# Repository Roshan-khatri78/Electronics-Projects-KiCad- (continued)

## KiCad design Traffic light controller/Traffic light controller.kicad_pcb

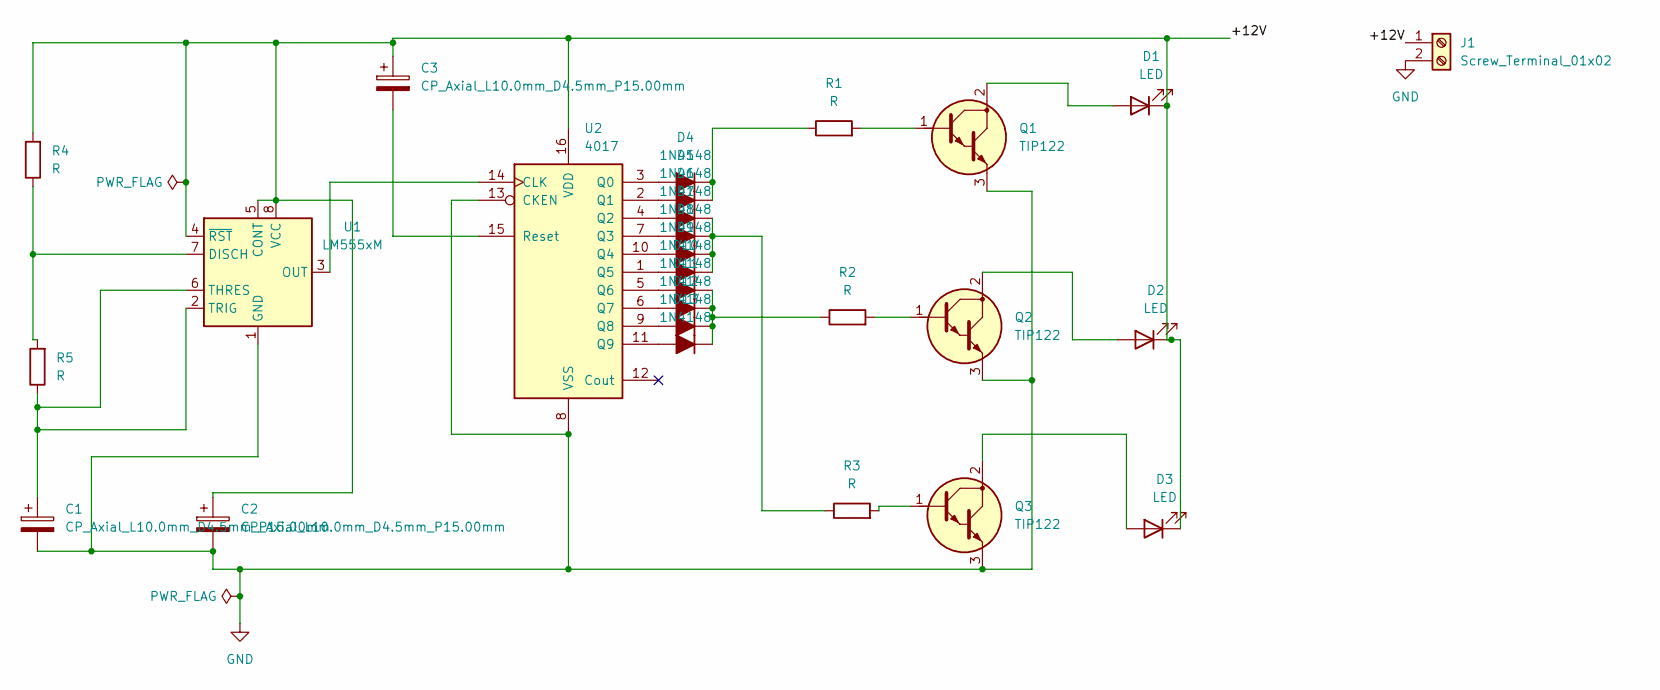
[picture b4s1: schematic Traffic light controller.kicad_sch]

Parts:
C1, C2, C3: CP_Axial_L10.0mm_D4.5mm_P15.00mm; CP_Axial_L10.0mm_D4.5mm_P15.00mm_Horizontal
D1, D2, D3: LED; LED_D5.0mm
D4, D5, D6, D7, D8, D9, D10, D11, D12, D13: 1N4148; D_5W_P12.70mm_Horizontal
J1: Screw_Terminal_01x02; TerminalBlock_MaiXu_MX126-5.0-02P_1x02_P5.00mm
Q1, Q2, Q3: TIP122; TO-220-3_Vertical_BCE
R1, R2, R3, R4, R5: R; R_Axial_DIN0204_L3.6mm_D1.6mm_P1.90mm_Vertical
U1: LM555xM; SOIC-8_3.9x4.9mm_P1.27mm
U2: 4017; DIP-16_W10.16mm

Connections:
/+12V: C2.1, C3.1, D1.1 (K), D2.1 (K), D3.1 (K), J1.1, R4.2, U1.4 (~RST), U1.5 (CONT), U1.8 (VCC), U2.16 (VDD)
GND: C1.2, C2.2, J1.2, Q1.3 (E), Q2.3 (E), Q3.3 (E), U1.1 (GND), U2.8 (VSS), U2.13 (CKEN)
unnamed: D1.2 (A), Q1.2 (C)
unnamed: D2.2 (A), Q2.2 (C)
unnamed: D3.2 (A), Q3.2 (C)
unnamed: D4.2 (A), U2.3 (Q0)
unnamed: D4.1 (K), D5.1 (K), R1.1
unnamed: D5.2 (A), U2.2 (Q1)
unnamed: D6.2 (A), U2.4 (Q2)
unnamed: D6.1 (K), D7.1 (K), D8.1 (K), D9.1 (K), R3.1
unnamed: D7.2 (A), U2.7 (Q3)
unnamed: D8.2 (A), U2.10 (Q4)
unnamed: D9.2 (A), U2.1 (Q5)
unnamed: D10.2 (A), U2.5 (Q6)
unnamed: D10.1 (K), D11.1 (K), D12.1 (K), D13.1 (K), R2.1
unnamed: D11.2 (A), U2.6 (Q7)
unnamed: D12.2 (A), U2.9 (Q8)
unnamed: D13.2 (A), U2.11 (Q9)
unnamed: Q1.1 (B), R1.2
unnamed: Q2.1 (B), R2.2
unnamed: Q3.1 (B), R3.2
unnamed: R4.1, R5.2, U1.7 (DISCH)
unnamed: U1.3 (OUT), U2.14 (CLK)
unnamed: C1.1, R5.1, U1.2 (TRIG), U1.6 (THRES)
unnamed: C3.2, U2.15 (Reset)

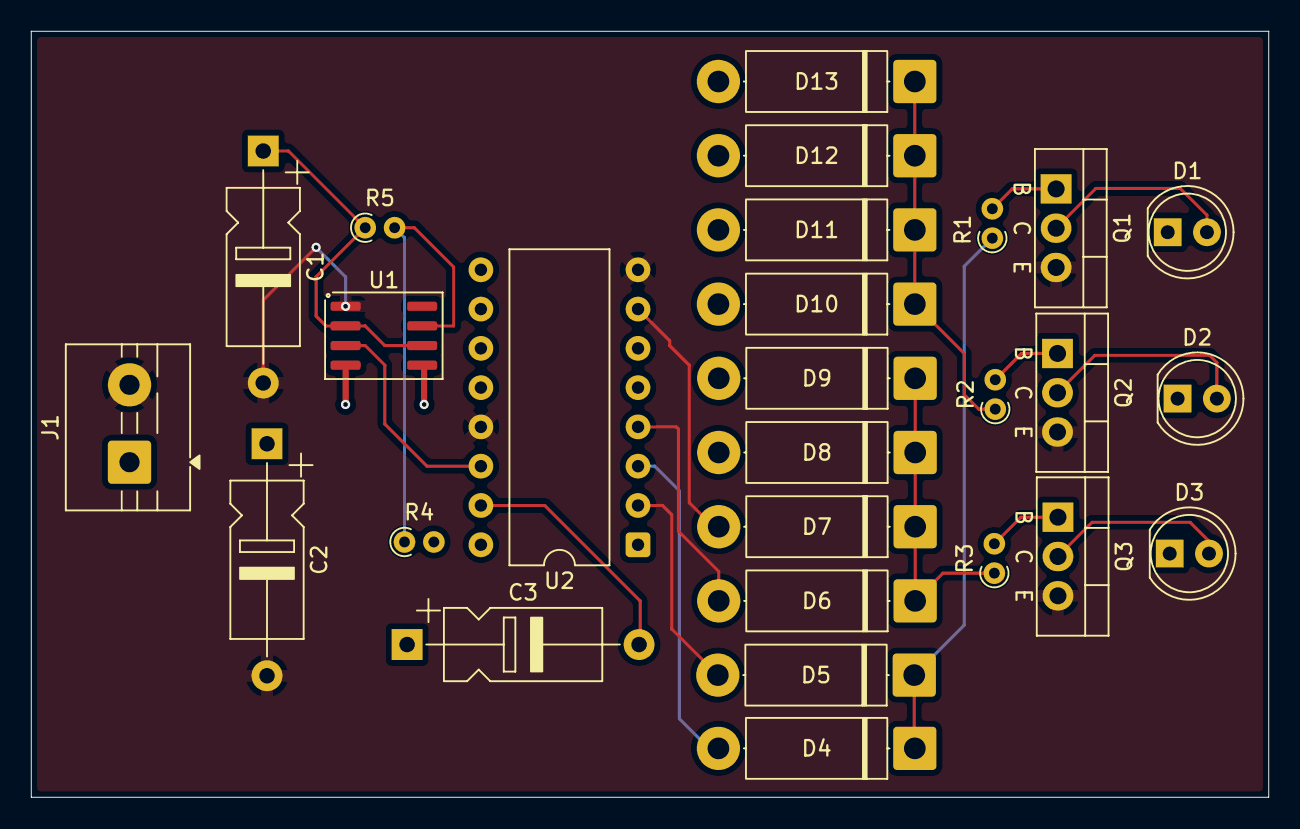
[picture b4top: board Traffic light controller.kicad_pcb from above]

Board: 4 copper layers, 80.0 x 49.5 mm, 27 parts (0 on the bottom side), 25 nets.

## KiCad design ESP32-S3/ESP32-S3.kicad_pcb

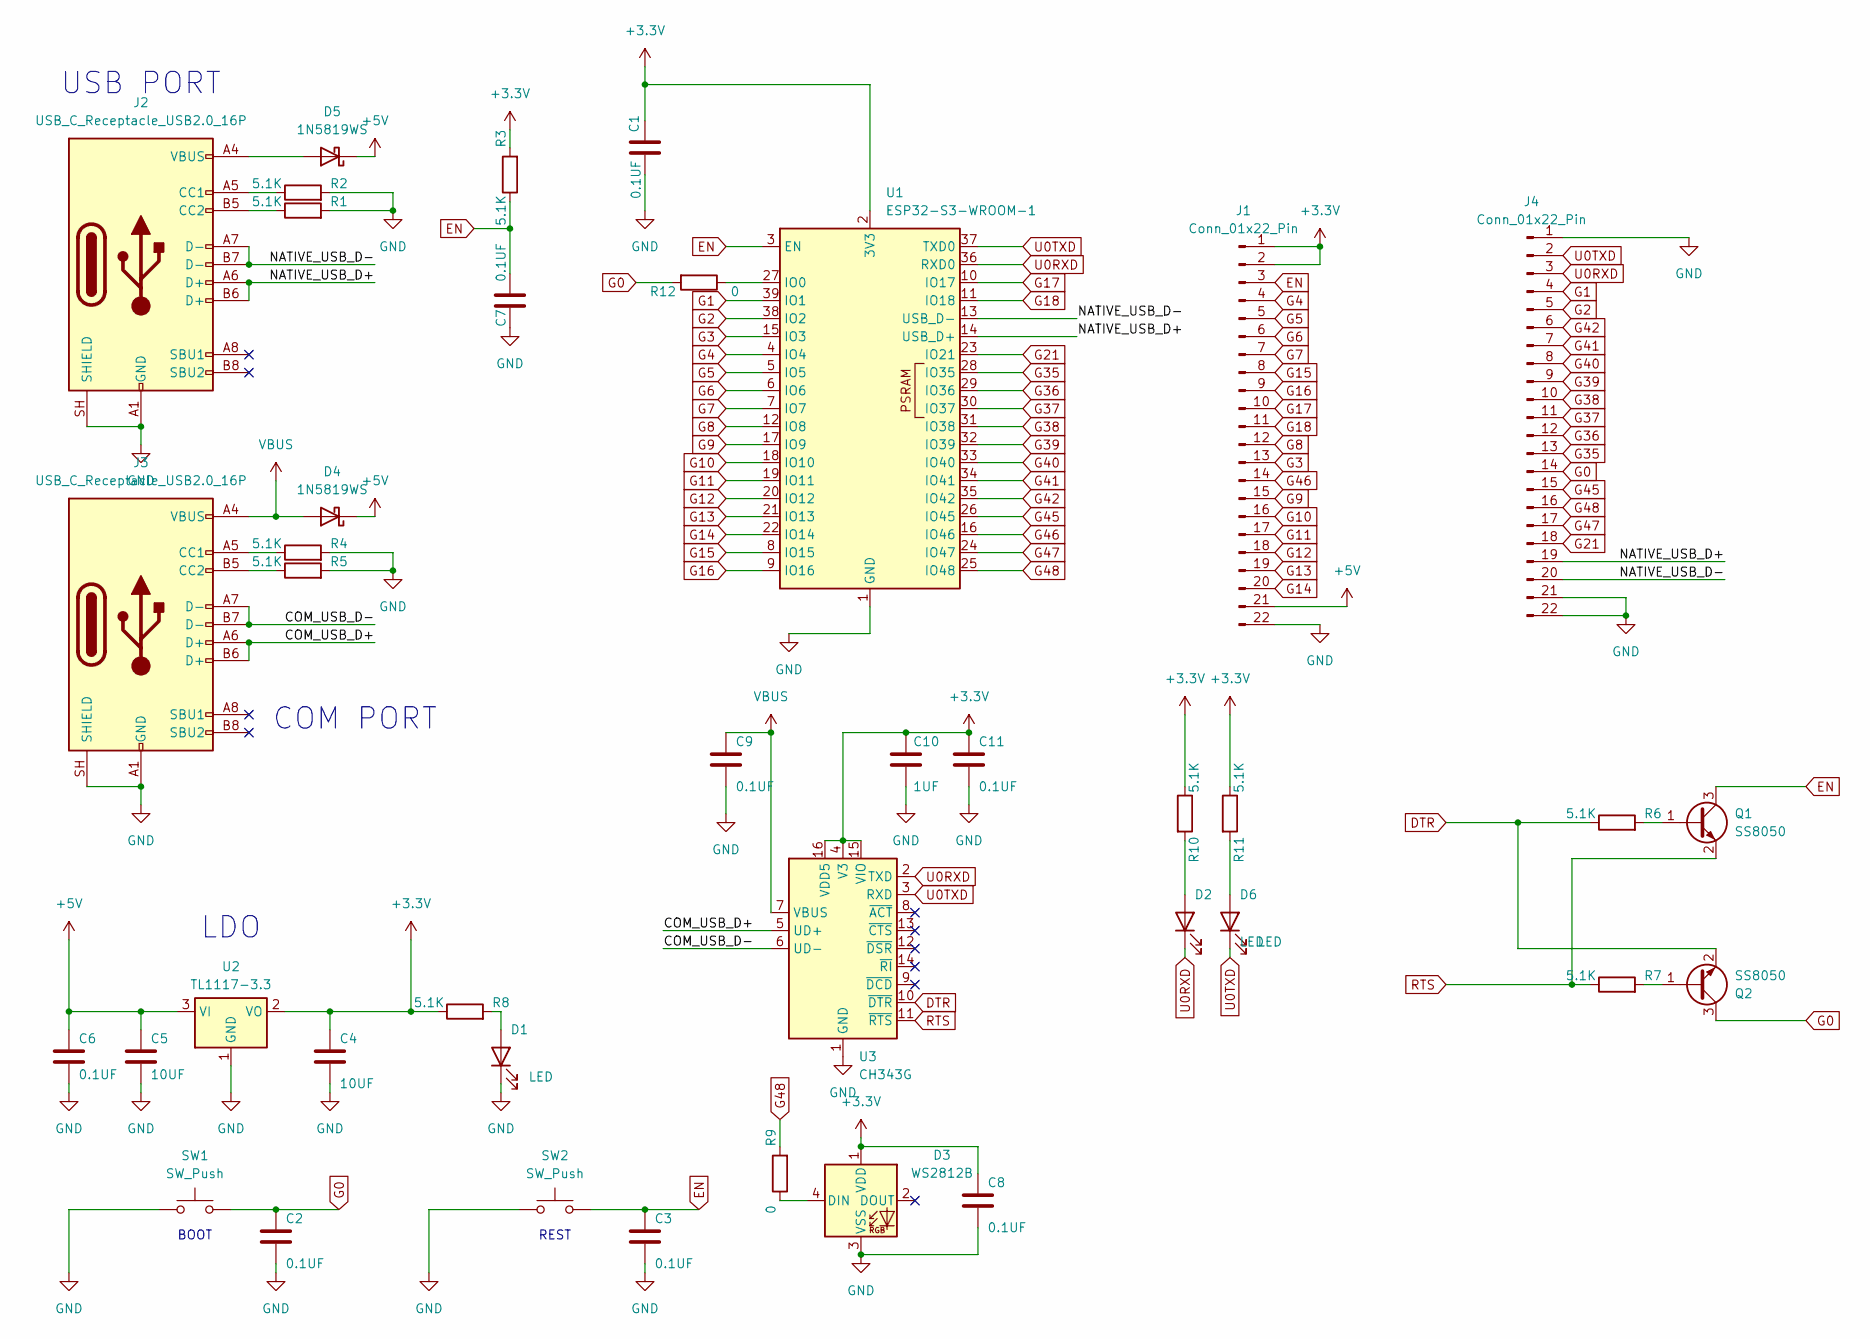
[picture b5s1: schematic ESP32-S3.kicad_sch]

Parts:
C1, C2, C3, C6, C7, C8, C9, C11: 0.1UF; C_0603_1608Metric
C4, C5: 10UF; C_0805_2012Metric
C10: 1UF; C_0603_1608Metric
D1, D2, D6: LED; LED_0603_1608Metric_Pad1.05x0.95mm_HandSolder
D3: WS2812B; LED_WS2812B_PLCC4_5.0x5.0mm_P3.2mm
D4, D5: 1N5819WS; D_SOD-323
J1, J4: Conn_01x22_Pin; PinHeader_1x22_P2.54mm_Vertical
J2, J3: USB_C_Receptacle_USB2.0_16P; USB_C_Receptacle_GCT_USB4105-xx-A_16P_TopMnt_Horizontal
Q1, Q2: SS8050; SOT-23
R1, R2, R3, R4, R5, R6, R7, R8, R10, R11: 5.1K; R_0603_1608Metric
R9, R12: 0; R_0603_1608Metric
SW1, SW2: SW_Push; SW_SPST_PTS810
U1: ESP32-S3-WROOM-1
U2: TL1117-3.3; SOT-223-3_TabPin2
U3: CH343G; SOIC-16_3.9x9.9mm_P1.27mm

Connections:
+3.3V: C1.1, C4.1, C8.1, C10.2, C11.2, D3.1 (VDD), J1.1, J1.2, R3.2, R8.1, R10.1, R11.1, U1.2 (3V3), U2.2 (VO), U3.4 (V3), U3.15 (VIO), U3.16 (VDD5)
+5V: C5.1, C6.1, D4.1 (K), D5.1 (K), J1.21, U2.3 (VI)
/COM_USB_D+: J3.A6 (D+), J3.B6 (D+), U3.5 (UD+)
/COM_USB_D-: J3.A7 (D-), J3.B7 (D-), U3.6 (UD-)
/NATIVE_USB_D+: J2.A6 (D+), J2.B6 (D+), J4.19, U1.14 (USB_D+)
/NATIVE_USB_D-: J2.A7 (D-), J2.B7 (D-), J4.20, U1.13 (USB_D-)
DTR: Q2.2 (E), R6.1, U3.10 (~DTR)
EN: C3.1, C7.1, J1.3, Q1.3 (C), R3.1, SW2.2, U1.3 (EN); also elsewhere on the board
G0: C2.1, J4.14, Q2.3 (C), R12.2, SW1.2; also elsewhere on the board
G1: J4.4, U1.39 (IO1)
G2: J4.5, U1.38 (IO2)
G3: J1.13, U1.15 (IO3)
G4: J1.4, U1.4 (IO4)
G5: J1.5, U1.5 (IO5)
G6: J1.6, U1.6 (IO6)
G7: J1.7, U1.7 (IO7)
G8: J1.12, U1.12 (IO8)
G9: J1.15, U1.17 (IO9)
G10: J1.16, U1.18 (IO10)
G11: J1.17, U1.19 (IO11)
G12: J1.18, U1.20 (IO12)
G13: J1.19, U1.21 (IO13)
G14: J1.20, U1.22 (IO14)
G15: J1.8, U1.8 (IO15)
G16: J1.9, U1.9 (IO16)
G17: J1.10, U1.10 (IO17)
G18: J1.11, U1.11 (IO18)
G21: J4.18, U1.23 (IO21)
G35: J4.13, U1.28 (IO35)
G36: J4.12, U1.29 (IO36)
G37: J4.11, U1.30 (IO37)
G38: J4.10, U1.31 (IO38)
G39: J4.9, U1.32 (IO39)
G40: J4.8, U1.33 (IO40)
G41: J4.7, U1.34 (IO41)
G42: J4.6, U1.35 (IO42)
G45: J4.15, U1.26 (IO45)
G46: J1.14, U1.16 (IO46)
G47: J4.17, U1.24 (IO47)
G48: J4.16, R9.2, U1.25 (IO48)
GND: C1.2, C2.2, C3.2, C4.2, C5.2, C6.2, C7.2, C8.2, C9.1, C10.1, C11.1, D1.1 (K), D3.3 (VSS), J1.22, J2.A1 (GND), J2.A12 (GND), J2.B1 (GND), J2.B12 (GND), J2.SH (SHIELD), J3.A1 (GND), J3.A12 (GND), J3.B1 (GND), J3.B12 (GND), J3.SH (SHIELD), J4.1, J4.21, J4.22, R1.2, R2.2, R4.2, R5.2, SW1.1, SW2.1, U1.1 (GND), U1.40 (GND), U1.41 (GND), U2.1 (GND), U3.1 (GND); also elsewhere on the board
unnamed: D1.2 (A), R8.2
unnamed: D2.2 (A), R10.2
unnamed: D3.4 (DIN), R9.1
unnamed: D5.2 (A), J2.A4 (VBUS), J2.A9 (VBUS), J2.B4 (VBUS), J2.B9 (VBUS)
unnamed: D6.2 (A), R11.2
unnamed: J2.A5 (CC1), R2.1
unnamed: J2.B5 (CC2), R1.1
unnamed: J3.A5 (CC1), R4.1
unnamed: J3.B5 (CC2), R5.1
unnamed: Q1.1 (B), R6.2
unnamed: Q2.1 (B), R7.2
unnamed: R12.1, U1.27 (IO0)
RTS: Q1.2 (E), R7.1, U3.11 (~RTS)
U0RXD: D2.1 (K), J4.3, U1.36 (RXD0), U3.2 (TXD)
U0TXD: D6.1 (K), J4.2, U1.37 (TXD0), U3.3 (RXD)
VBUS: C9.2, D4.2 (A), J3.A4 (VBUS), J3.A9 (VBUS), J3.B4 (VBUS), J3.B9 (VBUS), U3.7 (VBUS)

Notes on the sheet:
COM PORT
REST
LDO
USB PORT
BOOT

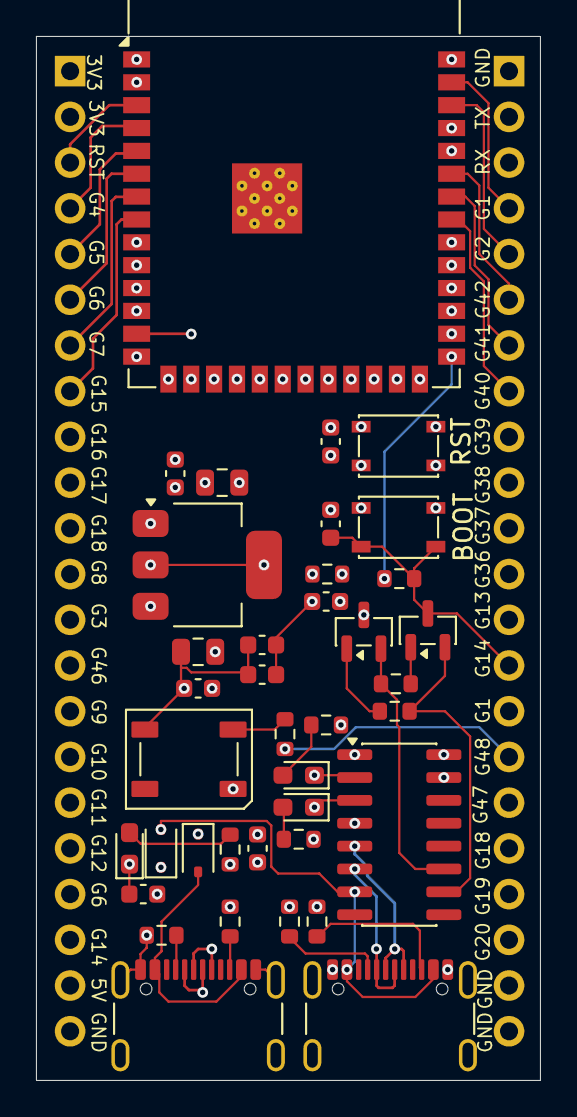
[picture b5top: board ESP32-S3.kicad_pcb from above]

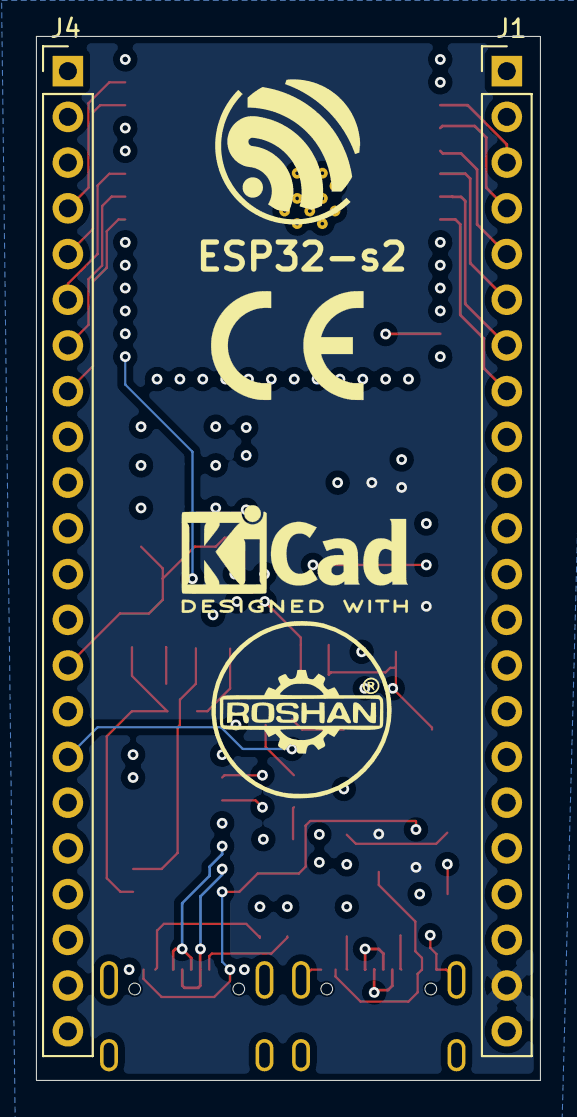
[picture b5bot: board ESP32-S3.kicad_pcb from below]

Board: 4 copper layers, 28.0 x 58.0 mm, 40 parts (2 on the bottom side), 57 nets.

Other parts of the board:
BOOT: SW_Push; SW_SPST_PTS810
RST: SW_Push; SW_SPST_PTS810

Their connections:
EN: RST.2; also elsewhere on the board
G0: BOOT.2; also elsewhere on the board
GND: BOOT.1, RST.1; also elsewhere on the board

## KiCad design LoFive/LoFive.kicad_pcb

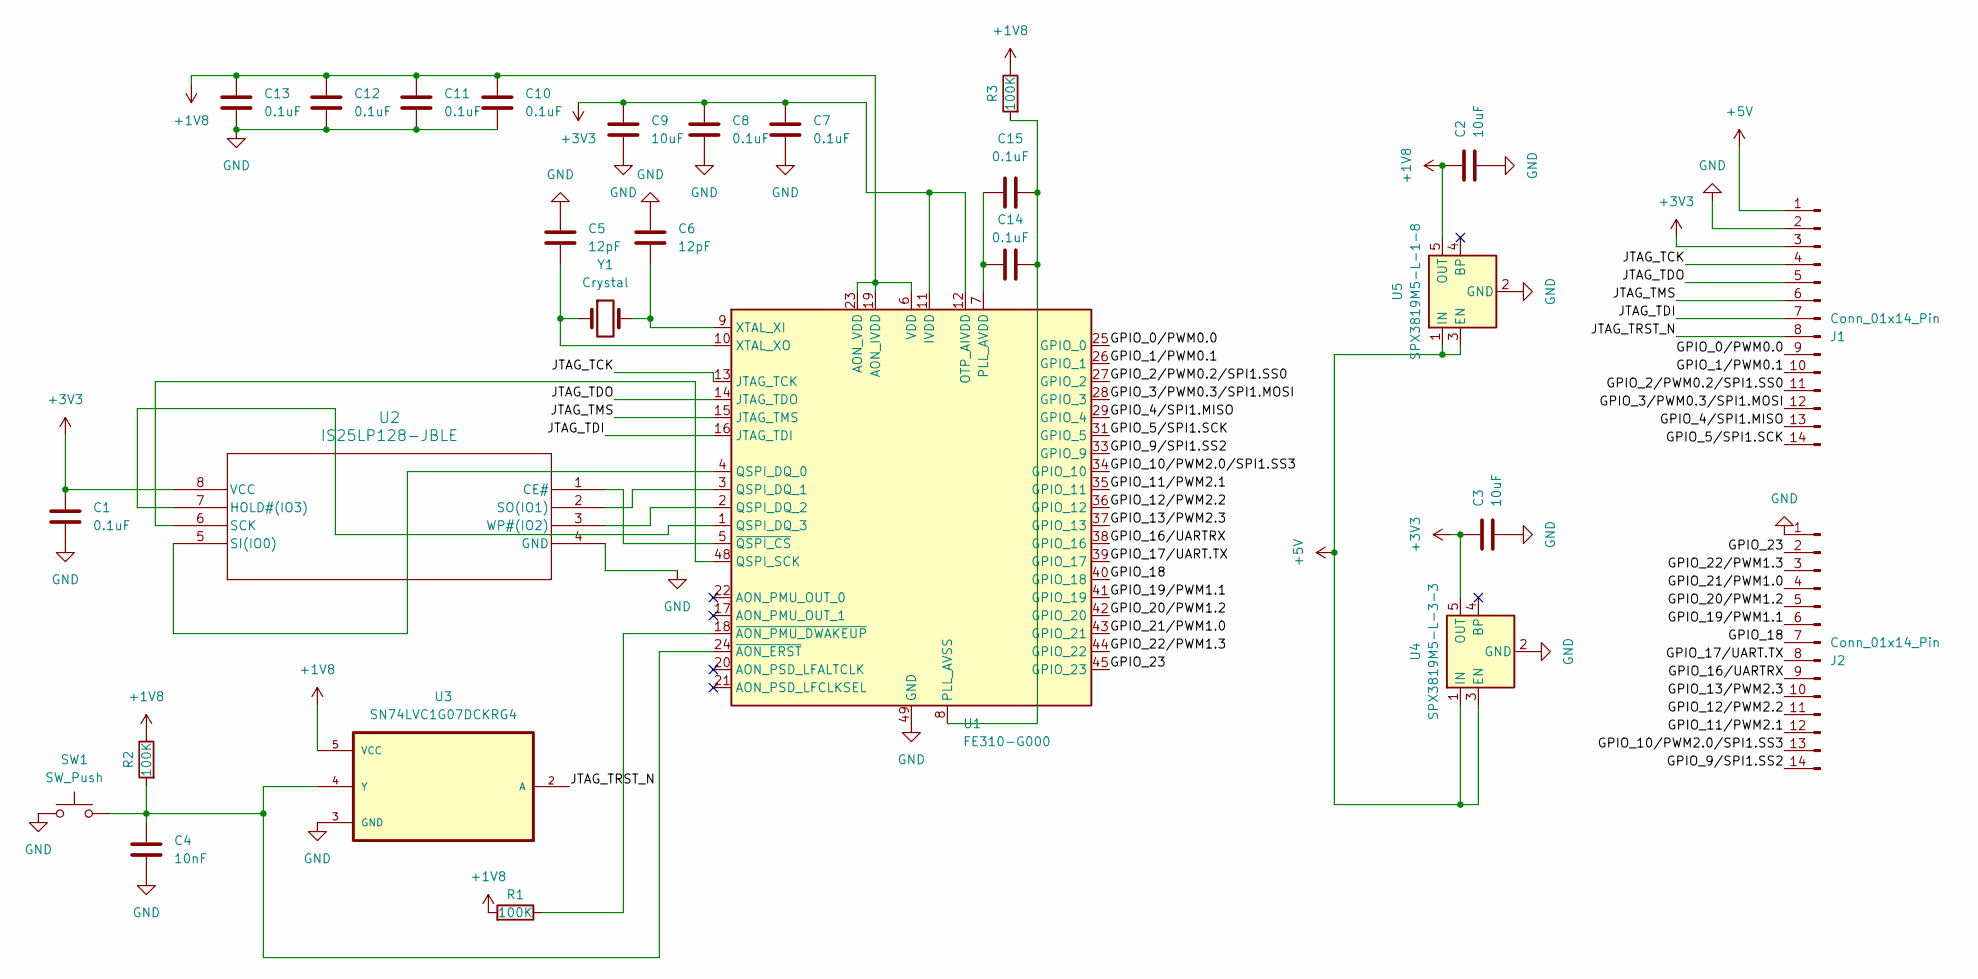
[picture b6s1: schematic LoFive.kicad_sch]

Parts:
C1, C7, C8, C10, C11, C12, C13, C14, C15: 0.1uF; C_0402_1005Metric_Pad0.74x0.62mm_HandSolder
C2, C3, C9: 10uF; C_0402_1005Metric_Pad0.74x0.62mm_HandSolder
C4: 10nF; C_0402_1005Metric_Pad0.74x0.62mm_HandSolder
C5, C6: 12pF; C_0402_1005Metric_Pad0.74x0.62mm_HandSolder
J1, J2: Conn_01x14_Pin; PinHeader_1x14_P2.54mm_Vertical
R1, R2, R3: 100K; R_0402_1005Metric_Pad0.72x0.64mm_HandSolder
SW1: SW_Push; SW_PUSH_6mm_H5mm
U1: FE310-G000; QFN-48-1EP_6x6mm_P0.4mm_EP4.2x4.2mm_ThermalVias
U2: IS25LP128-JBLE; SOIC8_208MIL_JB_ISI-M
U3: SN74LVC1G07DCKRG4; SOT65P210X110-5N
U4: SPX3819M5-L-3-3; SOT-23-5
U5: SPX3819M5-L-1-8; SOT-23-5
Y1: Crystal; Crystal_SMD_HC49-SD

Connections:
+1V8: C2.1, C10.1, C11.1, C12.1, C13.1, R1.1, R2.2, R3.2, U1.6 (VDD), U1.19 (AON_IVDD), U1.23 (AON_VDD), U1.30 (VDD), U1.46 (VDD), U3.5 (VCC), U5.5 (OUT)
+3V3: C1.1, C3.1, C7.1, C8.1, C9.1, J1.3, U1.11 (IVDD), U1.12 (OTP_AIVDD), U1.32 (IVDD), U1.47 (IVDD), U2.8 (VCC), U4.5 (OUT)
+5V: J1.1, U4.1 (IN), U4.3 (EN), U5.1 (IN), U5.3 (EN)
/GPIO_0/PWM0.0: J1.9, U1.25 (GPIO_0)
/GPIO_1/PWM0.1: J1.10, U1.26 (GPIO_1)
/GPIO_2/PWM0.2/SPI1.SS0: J1.11, U1.27 (GPIO_2)
/GPIO_3/PWM0.3/SPI1.MOSI: J1.12, U1.28 (GPIO_3)
/GPIO_4/SPI1.MISO: J1.13, U1.29 (GPIO_4)
/GPIO_5/SPI1.SCK: J1.14, U1.31 (GPIO_5)
/GPIO_9/SPI1.SS2: J2.14, U1.33 (GPIO_9)
/GPIO_10/PWM2.0/SPI1.SS3: J2.13, U1.34 (GPIO_10)
/GPIO_11/PWM2.1: J2.12, U1.35 (GPIO_11)
/GPIO_12/PWM2.2: J2.11, U1.36 (GPIO_12)
/GPIO_13/PWM2.3: J2.10, U1.37 (GPIO_13)
/GPIO_16/UARTRX: J2.9, U1.38 (GPIO_16)
/GPIO_17/UART.TX: J2.8, U1.39 (GPIO_17)
/GPIO_18: J2.7, U1.40 (GPIO_18)
/GPIO_19/PWM1.1: J2.6, U1.41 (GPIO_19)
/GPIO_20/PWM1.2: J2.5, U1.42 (GPIO_20)
/GPIO_21/PWM1.0: J2.4, U1.43 (GPIO_21)
/GPIO_22/PWM1.3: J2.3, U1.44 (GPIO_22)
/GPIO_23: J2.2, U1.45 (GPIO_23)
/JTAG_TCK: J1.4, U1.13 (JTAG_TCK)
/JTAG_TDI: J1.7, U1.16 (JTAG_TDI)
/JTAG_TDO: J1.5, U1.14 (JTAG_TDO)
/JTAG_TMS: J1.6, U1.15 (JTAG_TMS)
/JTAG_TRST_N: J1.8, U3.2 (A)
GND: C1.2, C2.2, C3.2, C4.2, C5.1, C6.1, C7.2, C8.2, C9.2, C10.2, C11.2, C12.2, C13.2, J1.2, J2.1, SW1.1, U1.49 (GND), U2.4 (GND), U3.3 (GND), U4.2 (GND), U5.2 (GND)
unnamed: C14.1, C15.1, U1.7 (PLL_AVDD)
unnamed: C14.2, C15.2, R3.1, U1.8 (PLL_AVSS)
unnamed: U1.4 (QSPI_DQ_0), U2.5 (SI(IO0))
unnamed: U1.3 (QSPI_DQ_1), U2.2 (SO(IO1))
unnamed: U1.2 (QSPI_DQ_2), U2.3 (WP#(IO2))
unnamed: U1.1 (QSPI_DQ_3), U2.7 (HOLD#(IO3))
unnamed: U1.48 (QSPI_SCK), U2.6 (SCK)
unnamed: C6.2, U1.9 (XTAL_XI), Y1.2
unnamed: C5.2, U1.10 (XTAL_XO), Y1.1
unnamed: C4.1, R2.1, SW1.2, U1.24 (~AON_ERST), U3.4 (Y)
unnamed: R1.2, U1.18 (~AON_PMU_DWAKEUP)
unnamed: U1.5 (~QSPI_CS), U2.1 (CE#)

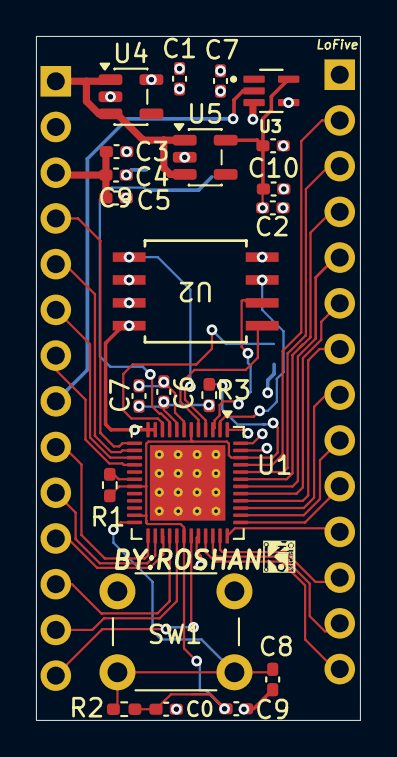
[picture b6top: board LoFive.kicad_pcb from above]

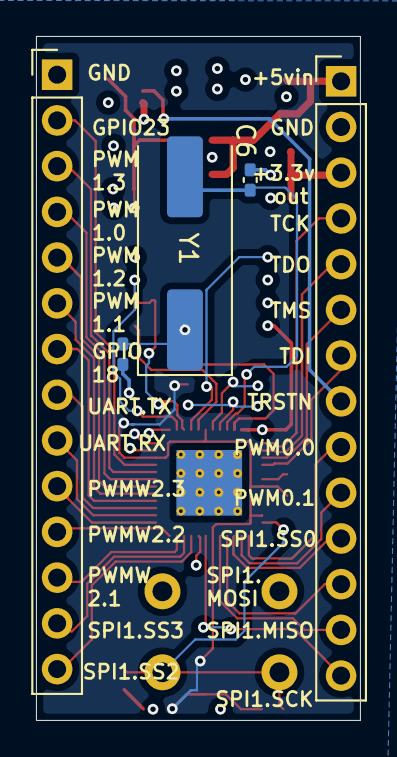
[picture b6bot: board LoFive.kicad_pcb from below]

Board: 4 copper layers, 18.0 x 38.0 mm, 27 parts (5 on the bottom side), 40 nets.

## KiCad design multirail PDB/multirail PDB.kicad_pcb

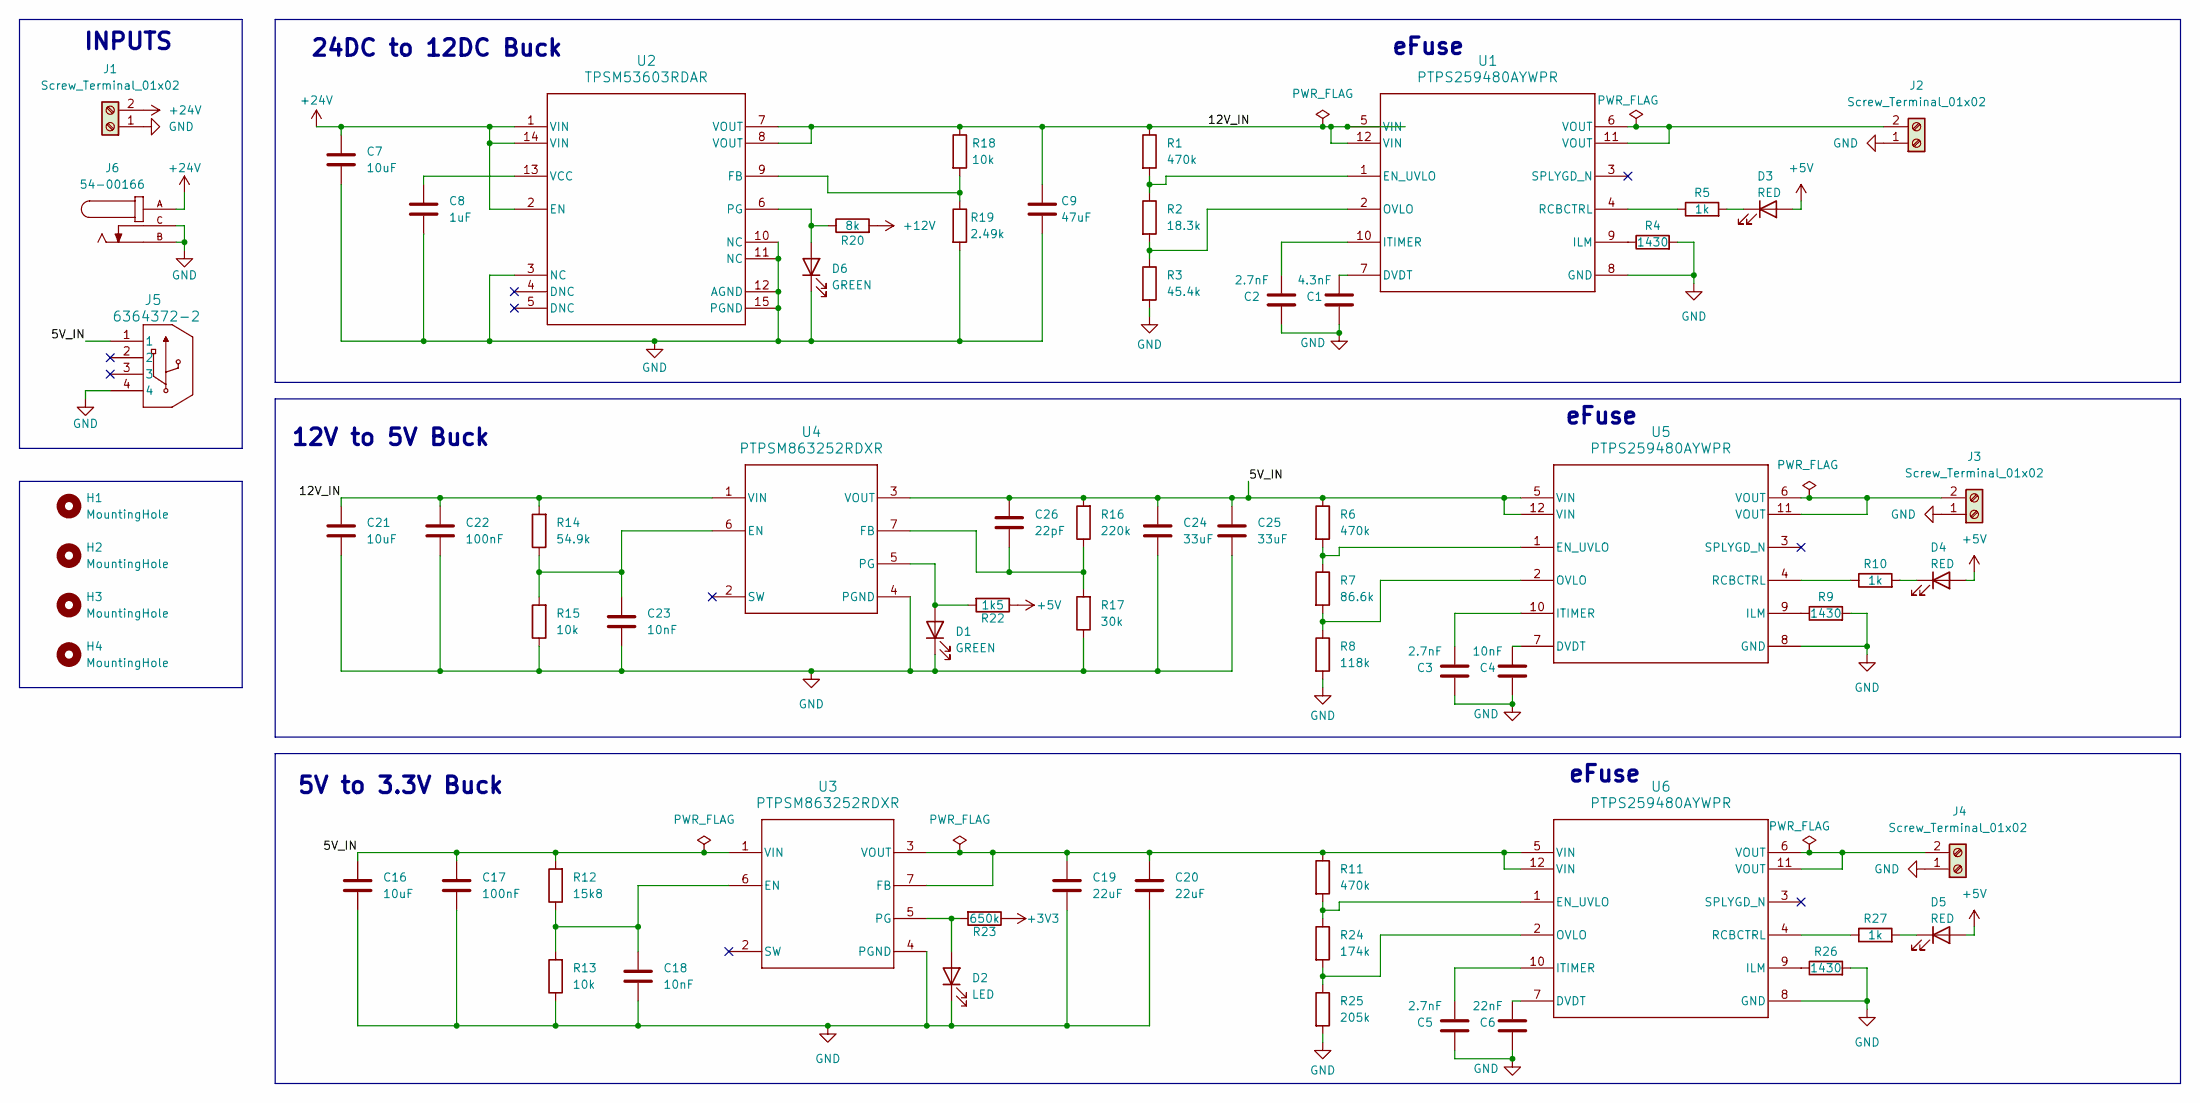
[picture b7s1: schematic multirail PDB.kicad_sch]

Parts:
C1: 4.3nF; C_0805_2012Metric_Pad1.18x1.45mm_HandSolder
C2, C3, C5: 2.7nF; C_0805_2012Metric_Pad1.18x1.45mm_HandSolder
C4: 10nF; C_0805_2012Metric_Pad1.18x1.45mm_HandSolder
C6: 22nF; C_0805_2012Metric_Pad1.18x1.45mm_HandSolder
C7: 10uF; C_0805_2012Metric_Pad1.18x1.45mm_HandSolder
C8: 1uF; C_0805_2012Metric_Pad1.18x1.45mm_HandSolder
C9: 47uF; C_0805_2012Metric_Pad1.18x1.45mm_HandSolder
C16, C21: 10uF; R_0805_2012Metric_Pad1.20x1.40mm_HandSolder
C17, C22: 100nF; R_0805_2012Metric_Pad1.20x1.40mm_HandSolder
C18: 10nF; C_0603_1608Metric_Pad1.08x0.95mm_HandSolder
C19, C20: 22uF; R_0805_2012Metric_Pad1.20x1.40mm_HandSolder
C23: 10nF; R_0603_1608Metric_Pad0.98x0.95mm_HandSolder
C24, C25: 33uF; R_0805_2012Metric_Pad1.20x1.40mm_HandSolder
C26: 22pF; R_0805_2012Metric_Pad1.20x1.40mm_HandSolder
D1, D6: GREEN; LED_0603_1608Metric_Pad1.05x0.95mm_HandSolder
D2: LED; LED_0603_1608Metric_Pad1.05x0.95mm_HandSolder
D3, D4, D5: RED; LED_0603_1608Metric_Pad1.05x0.95mm_HandSolder
H1, H2, H3, H4: MountingHole; MountingHole_3.2mm_M3
J1, J2, J3, J4: Screw_Terminal_01x02; TerminalBlock_Phoenix_PT-1,5-2-5.0-H_1x02_P5.00mm_Horizontal
J5: 6364372-2; USB_A_Connfly_DS1095
J6: 54-00166; TENSILITY_54-00166; PARTREV A
R1, R6, R11: 470k; R_0805_2012Metric_Pad1.20x1.40mm_HandSolder
R2: 18.3k; R_0805_2012Metric_Pad1.20x1.40mm_HandSolder
R3: 45.4k; R_0805_2012Metric_Pad1.20x1.40mm_HandSolder
R4, R9, R26: 1430; R_0805_2012Metric_Pad1.20x1.40mm_HandSolder
R5, R10, R27: 1k; R_0805_2012Metric_Pad1.20x1.40mm_HandSolder
R7: 86.6k; R_0805_2012Metric_Pad1.20x1.40mm_HandSolder
R8: 118k; R_0805_2012Metric_Pad1.20x1.40mm_HandSolder
R12: 15k8; R_0603_1608Metric_Pad0.98x0.95mm_HandSolder
R13, R15: 10k; R_0603_1608Metric_Pad0.98x0.95mm_HandSolder
R14: 54.9k; R_0603_1608Metric_Pad0.98x0.95mm_HandSolder
R16: 220k; R_0603_1608Metric_Pad0.98x0.95mm_HandSolder
R17: 30k; R_0603_1608Metric_Pad0.98x0.95mm_HandSolder
R18: 10k; R_0805_2012Metric_Pad1.20x1.40mm_HandSolder
R19: 2.49k; R_0805_2012Metric_Pad1.20x1.40mm_HandSolder
R20: 8k; R_0805_2012Metric_Pad1.20x1.40mm_HandSolder
R22: 1k5; R_0603_1608Metric_Pad0.98x0.95mm_HandSolder
R23: 650k; R_0603_1608Metric_Pad0.98x0.95mm_HandSolder
R24: 174k; R_0805_2012Metric_Pad1.20x1.40mm_HandSolder
R25: 205k; R_0805_2012Metric_Pad1.20x1.40mm_HandSolder
U1, U5, U6: PTPS259480AYWPR; YWP0012A-MFG
U2: TPSM53603RDAR
U3, U4: PTPSM863252RDXR; RDX0007A-MFG

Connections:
+3V3: R23.1
+5V: D3.2 (A), D4.2 (A), D5.2 (A), R22.1
+12V: R20.2
+24V: C7.1, J1.2, J6.A, U2.1 (VIN), U2.2 (EN), U2.14 (VIN)
/5V_IN: C16.1, C17.1, C24.1, C25.1, C26.1, J5.1, R6.1, R12.2, R16.2, U3.1 (VIN), U4.3 (VOUT), U5.5 (VIN), U5.12 (VIN)
/12V_IN: C9.1, C21.1, C22.1, R1.1, R14.2, R18.1, U1.5 (VIN), U1.12 (VIN), U2.7 (VOUT), U2.8 (VOUT), U4.1 (VIN)
GND: C1.1, C2.1, C3.1, C4.1, C5.1, C6.1, C7.2, C8.2, C9.2, C16.2, C17.2, C18.2, C19.2, C20.2, C21.2, C22.2, C23.2, C24.2, C25.2, D1.1 (K), D2.1 (K), D6.1 (K), J1.1, J2.1, J3.1, J4.1, J5.4, J6.B, J6.C, R3.2, R4.2, R8.2, R9.2, R13.1, R15.1, R17.1, R19.2, R25.2, R26.2, U1.8 (GND), U2.3 (NC), U2.10 (NC), U2.11 (NC), U2.12 (AGND), U2.15 (PGND), U3.4 (PGND), U4.4 (PGND), U5.8 (GND), U6.8 (GND)
unnamed: D1.2 (A), R22.2, U4.5 (PG)
unnamed: D2.2 (A), R23.2, U3.5 (PG)
unnamed: D3.1 (K), R5.2
unnamed: D4.1 (K), R10.2
unnamed: D5.1 (K), R27.2
unnamed: D6.2 (A), R20.1, U2.6 (PG)
unnamed: J2.2, U1.6 (VOUT), U1.11 (VOUT)
unnamed: J3.2, U5.6 (VOUT), U5.11 (VOUT)
unnamed: J4.2, U6.6 (VOUT), U6.11 (VOUT)
unnamed: C1.2, U1.7 (DVDT)
unnamed: R1.2, R2.1, U1.1 (EN_UVLO)
unnamed: R4.1, U1.9 (ILM)
unnamed: C2.2, U1.10 (ITIMER)
unnamed: R2.2, R3.1, U1.2 (OVLO)
unnamed: R5.1, U1.4 (RCBCTRL)
unnamed: R18.2, R19.1, U2.9 (FB)
unnamed: C8.1, U2.13 (VCC)
unnamed: C18.1, R12.1, R13.2, U3.6 (EN)
unnamed: C19.1, C20.1, R11.1, U3.3 (VOUT), U3.7 (FB), U6.5 (VIN), U6.12 (VIN)
unnamed: C23.1, R14.1, R15.2, U4.6 (EN)
unnamed: C26.2, R16.1, R17.2, U4.7 (FB)
unnamed: C4.2, U5.7 (DVDT)
unnamed: R6.2, R7.1, U5.1 (EN_UVLO)
unnamed: R9.1, U5.9 (ILM)
unnamed: C3.2, U5.10 (ITIMER)
unnamed: R7.2, R8.1, U5.2 (OVLO)
unnamed: R10.1, U5.4 (RCBCTRL)
unnamed: C6.2, U6.7 (DVDT)
unnamed: R11.2, R24.1, U6.1 (EN_UVLO)
unnamed: R26.1, U6.9 (ILM)
unnamed: C5.2, U6.10 (ITIMER)
unnamed: R24.2, R25.1, U6.2 (OVLO)
unnamed: R27.1, U6.4 (RCBCTRL)

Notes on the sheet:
24DC to 12DC Buck
5V to 3.3V Buck
INPUTS
12V to 5V Buck
eFuse

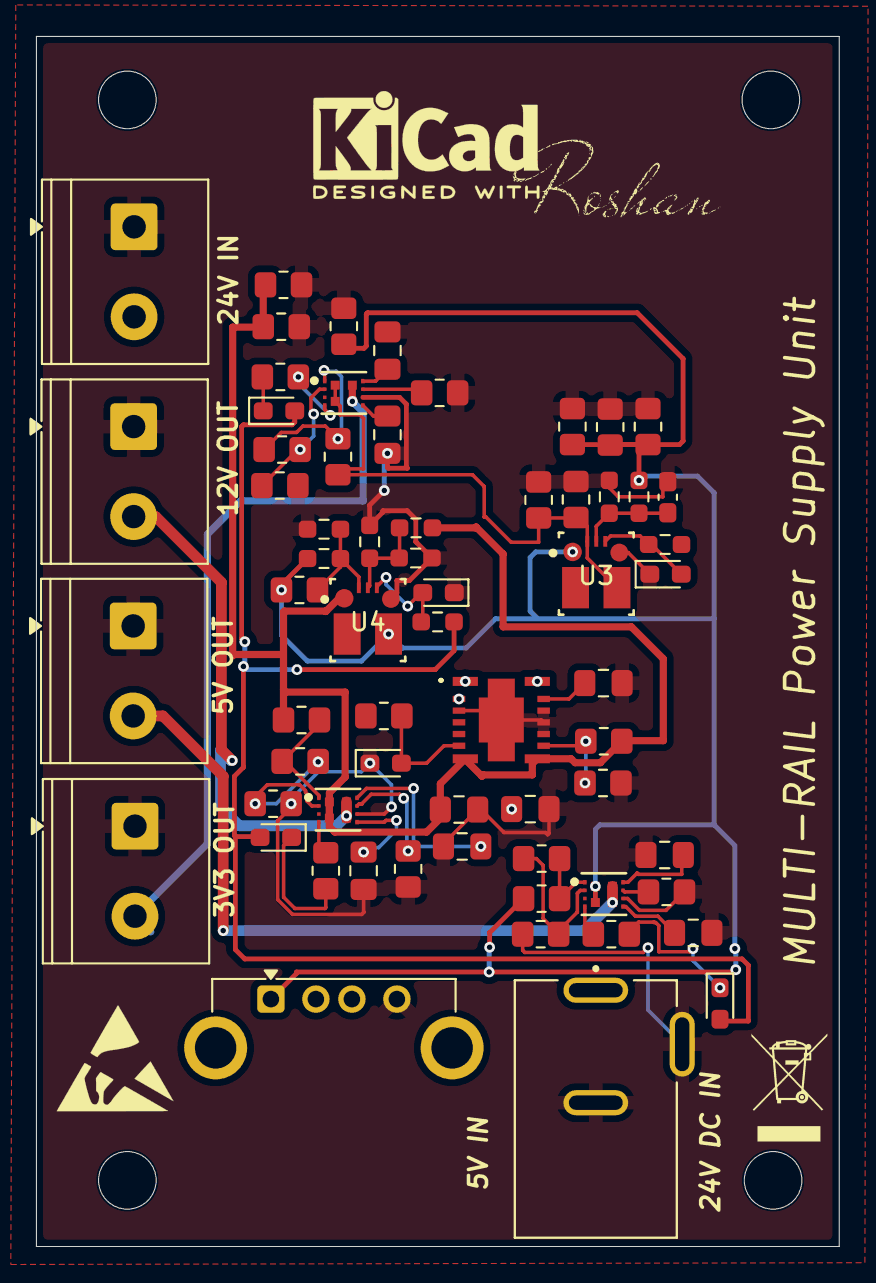
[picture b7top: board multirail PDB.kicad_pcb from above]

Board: 4 copper layers, 44.6 x 67.2 mm, 68 parts (0 on the bottom side), 38 nets.

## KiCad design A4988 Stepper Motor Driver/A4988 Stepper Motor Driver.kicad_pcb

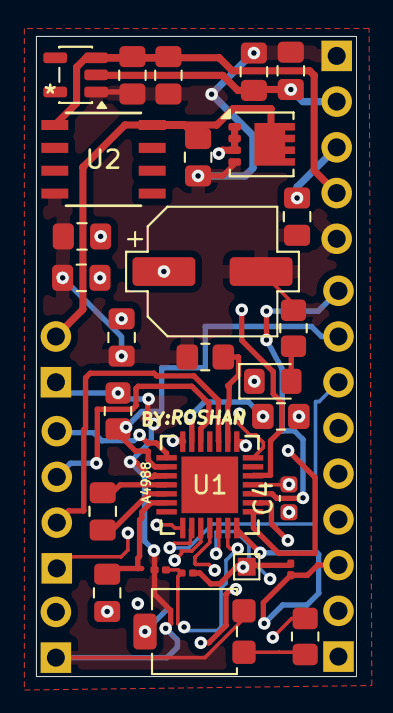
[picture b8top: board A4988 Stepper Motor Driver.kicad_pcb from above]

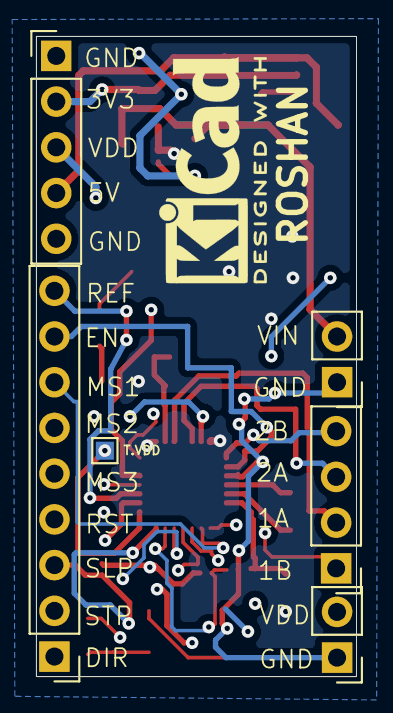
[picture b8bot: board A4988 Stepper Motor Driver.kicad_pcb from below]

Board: 4 copper layers, 17.8 x 35.6 mm, 34 parts (6 on the bottom side), 28 nets.

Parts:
C1: 47uF; C_0805_2012Metric_Pad1.18x1.45mm_HandSolder
C1#2: 47uF; CP_Elec_6.3x7.7
C2, C3, C7, C11: 0.1uF; C_0805_2012Metric_Pad1.18x1.45mm_HandSolder
C4: 0.22F; C_0603_1608Metric
C5: 0.22uF; C_0805_2012Metric_Pad1.18x1.45mm_HandSolder
C6: 0.47uF; C_0805_2012Metric_Pad1.18x1.45mm_HandSolder
C8: 10uF; C_0805_2012Metric_Pad1.18x1.45mm_HandSolder
C9, C10, C12: 4.7uF; C_0805_2012Metric_Pad1.18x1.45mm_HandSolder
D1: D_Schottky; D_0805_2012Metric_Pad1.15x1.40mm_HandSolder
J1: Conn_01x09_Pin; PinHeader_1x09_P2.54mm_Vertical
J2: Conn_01x04_Pin; PinHeader_1x04_P2.54mm_Vertical
J3: VDDin; PinHeader_1x02_P2.54mm_Vertical
J4: Conn_01x05_Pin; PinHeader_1x05_P2.54mm_Vertical
J5: Vin; PinHeader_1x02_P2.54mm_Vertical
Q1: DMP3013SFV; Diodes_PowerDI3333-8
R1, R3: 100K; R_0805_2012Metric_Pad1.20x1.40mm_HandSolder
R2: 20k; R_0805_2012Metric_Pad1.20x1.40mm_HandSolder
R4, R5: 100k; R_0201_0603Metric
R6: 10k; R_0201_0603Metric
R7, R8: 0.05; R_0805_2012Metric_Pad1.20x1.40mm_HandSolder
RV1: R_Potentiometer; Potentiometer_Bourns_3314G_Vertical
TP1, TP2: TestPoint_2Pole; TestPoint_Pad_1.0x1.0mm
U1: A4988SETTR-T; QFN-28_ALM
U2: NCV4264D50R2G; SOIC-8_NB_ONS
U3: ZLDO1117G12TA; SOT-23-5

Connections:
/1A: J2.2, U1.24 (OUT1A)
/1B: J2.1, U1.21 (OUT1B)
/2A: J2.3, U1.26 (OUT2A)
/2B: J2.4, U1.1 (OUT2B)
/3V3: C10.1, C11.1, J4.2, R2.1, U3.2 (OUT)
/5V: C8.1, C9.1, J4.4, U2.1 (VOUT), U3.3 (IN)
/DIR: J1.1, U1.19 (DIR)
/EN: J1.8, R3.1, U1.2 (*ENABLE)
/MS1: J1.7, U1.9 (MS1)
/MS2: J1.6, U1.10 (MS2)
/MS3: J1.5, U1.11 (MS3)
/REF: J1.9, RV1.2, U1.17 (REF)
/RST: J1.4, U1.12 (*RESET)
/S1: R7.1, U1.23 (SENSE1)
/S2: R8.1, U1.27 (SENSE2)
/SLP: J1.3, R5.2, U1.14 (*SLEEP)
/STP: J1.2, U1.16 (STEP)
/VDD: C5.1, J3.2, J4.3, R4.1, R5.1, TP1.1 (1_1), TP2.1 (1_1), U1.15 (VDD)
/VIN: C12.1, J5.2, Q1.5 (D), U2.8 (VIN)
/VMM: C1.1, C1#2.1, C3.1, C6.1, C7.1, D1.1 (K), Q1.1 (S), Q1.2 (S), Q1.3 (S), U1.22 (VBB1), U1.28 (VBB2)
/VREG: C4.1, U1.8 (VREG)
GND: C1.2, C1#2.2, C4.2, C5.2, C6.2, C7.2, C8.2, C9.2, C10.2, C11.2, C12.2, J3.1, J4.1, J4.5, J5.1, Q1.4 (G), R1.1, R3.2, R6.1, R7.2, R8.2, RV1.3, U1.3 (GND), U1.18 (GND), U2.4 (GND), U3.1
unnamed: D1.2 (A), R1.2
unnamed: R2.2, RV1.1
unnamed: C2.2, U1.4 (CP1)
unnamed: C2.1, U1.5 (CP2)
unnamed: R4.2, R6.2, U1.13 (ROSC)
unnamed: C3.2, U1.6 (VCP)

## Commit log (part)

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2026-06-10 Revise README for KiCad projects portfolio
    Updated README to enhance project description, structure, and goals.
2026-06-10 Add new project files
2026-06-13 Added mini inverter KiCad project
2026-06-16 added smps project
2026-06-16 Revise README with new projects and details
    Updated project descriptions and added new projects including a 60W SMPS and a mini inverter. Enhanced details on key components and concepts for better clarity.
2026-06-16 Fix formatting in README for repository structure section
2026-06-16 Update README with repository structure and tools used
    Added detailed repository structure and project descriptions.
2026-06-17 Added L298 motor pcb
2026-06-23 Added new files
2026-06-28 Update README with new project descriptions and structure
2026-06-28 added new project
